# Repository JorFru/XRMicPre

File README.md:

XRMicPre
========

### Project on standby state. I already have a X32.

Mic preamp module for a poor man's digital mixer

History:
Behringer's XR12 and XR16 are a very powerful and cheap digital mixers, but don't have enough mic preamps for some applications.

This project allows you to get the full performance of this mixers on live and studio applications.

Desireable features:

- Combo entrada de micrófono con jack. jack hi-z
- 2x salida balanceada
- Control de la ganancia preciso y repetible. Control de ganancia con stepped o con potenciómetro digital + pantalla.
- HPF 80-100Hz
- Alimentación phantom (DC-DC/a baterías)

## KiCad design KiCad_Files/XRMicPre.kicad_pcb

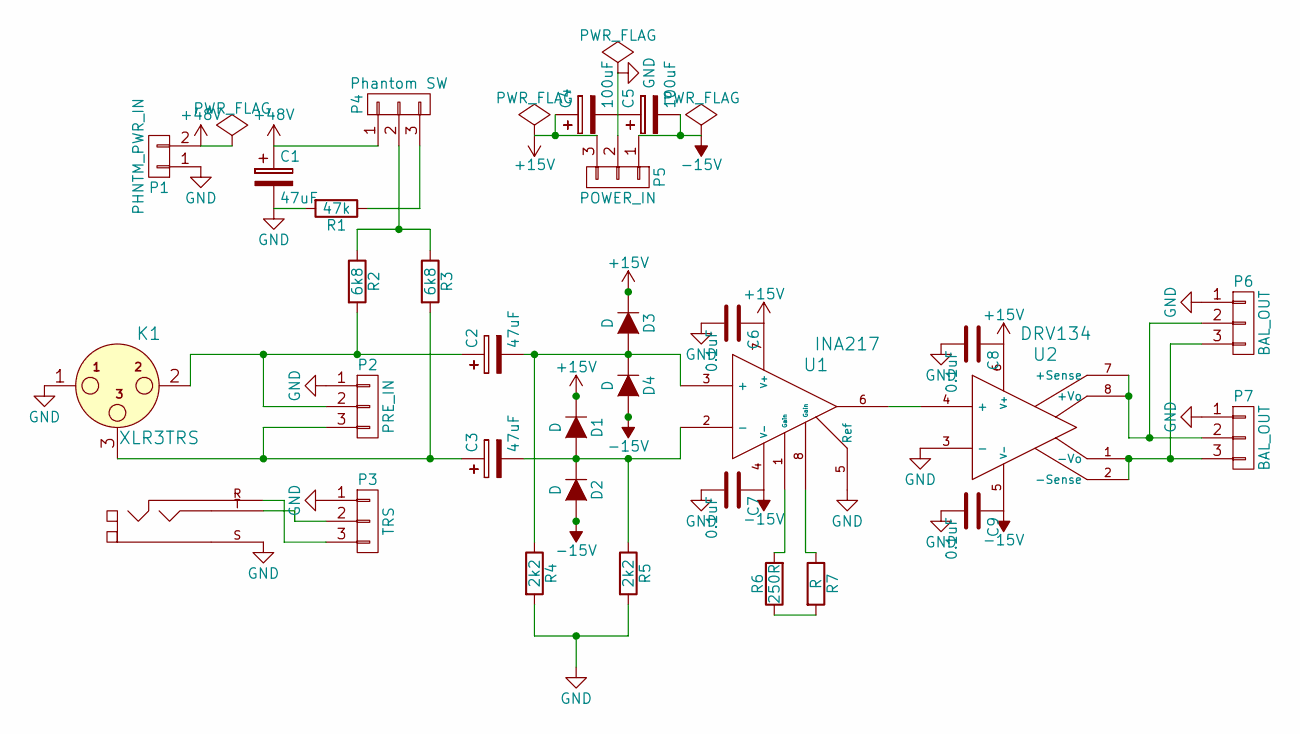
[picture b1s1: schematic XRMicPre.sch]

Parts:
C1, C2, C3: 47uF; C_Radial_D6.3_L11.2_P2.5
C4, C5: 100uF; C_Radial_D6.3_L11.2_P2.5
C6, C7, C8, C9: 0.1uF; C1-1
D1, D2, D3, D4: D; MiniMELF_Standard
K1: XLR3TRS; NCJ6FA-V
P1: PHNTM_PWR_IN; Socket_Strip_Straight_1x02
P2: PRE_IN; Socket_Strip_Straight_1x03
P3: TRS; Socket_Strip_Straight_1x03
P4: Phantom SW; Socket_Strip_Straight_1x03
P5: POWER_IN; Socket_Strip_Straight_1x03
P6, P7: BAL_OUT; Socket_Strip_Straight_1x03
R1: 47k; R_0805_HandSoldering
R2, R3: 6k8; R_0805_HandSoldering
R4, R5: 2k2; R_0805_HandSoldering
R6: 250R; R_0805_HandSoldering
R7: R; Socket_Strip_Straight_1x02
U1: INA217; DIP8+SOIC8_1
U2: DRV134; DIP8+SOIC8_1

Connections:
+15V: C4.1, C6.1, C8.1, D1.1 (K), D3.1 (K), P5.3, U1.7 (V+), U2.6 (V+)
+48V: C1.1, P1.2, P4.1
-15V: C5.2, C7.1, C9.1, D2.2 (A), D4.2 (A), P5.1, U1.4 (V-), U2.5 (V-)
GND: C1.2, C6.2, C7.2, C8.2, C9.2, K1.1, K1.S, P1.1, P2.1, P3.1, P5.2, P6.1, P7.1, R1.2, R4.2, R5.2, U1.5 (Ref), U2.3 (-)
unnamed: C2.1, K1.2, P2.2, R2.2
unnamed: C2.2, D3.2 (A), D4.1 (K), R4.1, U1.3 (+)
unnamed: C3.1, K1.3, P2.3, R3.2
unnamed: C3.2, D1.2 (A), D2.1 (K), R5.1, U1.2 (-)
unnamed: C4.2, C5.1
unnamed: K1.R, P3.3
unnamed: K1.T, P3.2
unnamed: P4.2, R2.1, R3.1
unnamed: P4.3, R1.1
unnamed: P6.2, P7.2, U2.7 (+Sense), U2.8 (+Vo)
unnamed: P6.3, P7.3, U2.1 (-Vo), U2.2 (-Sense)
unnamed: R6.1, R7.2
unnamed: R6.2, U1.1 (Gain)
unnamed: R7.1, U1.8 (Gain)
unnamed: U1.6, U2.4 (+)

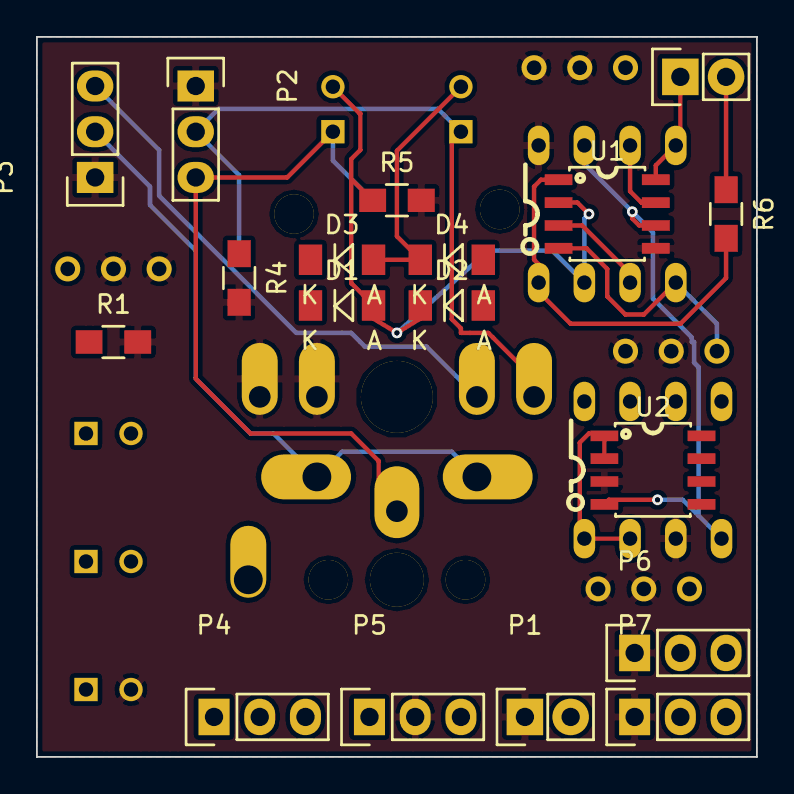
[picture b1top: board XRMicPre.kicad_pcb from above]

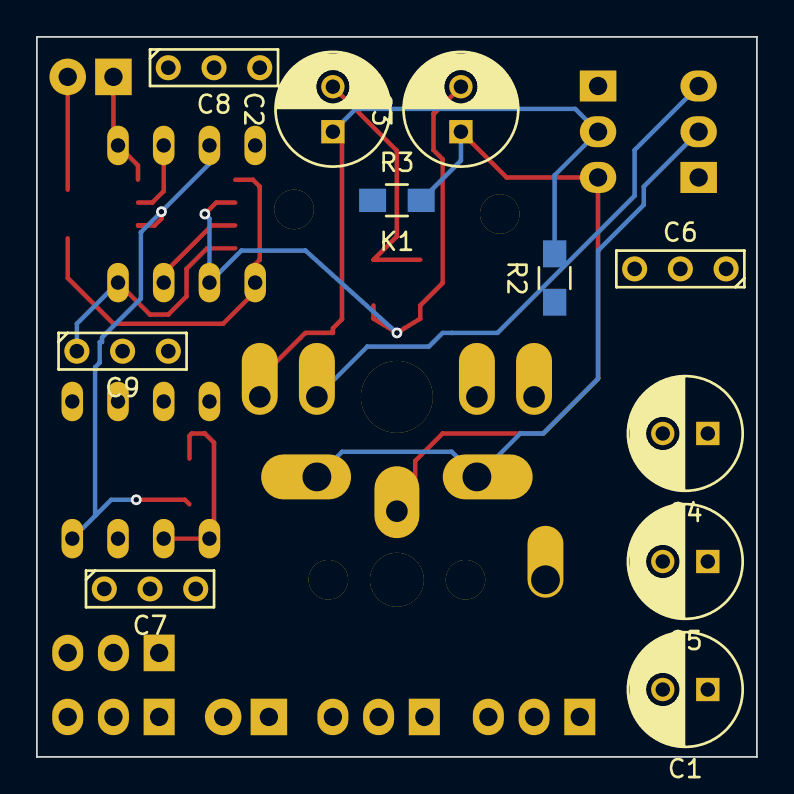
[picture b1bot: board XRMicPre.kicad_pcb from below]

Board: 2 copper layers, 40.0 x 40.0 mm, 30 parts (12 on the bottom side), 19 nets.

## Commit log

2016-03-17 Picture and readme upload
2016-03-18 Reduce picture weight
2016-03-18 Redimension pic
2016-03-18 Resized
2016-07-06 First commit for KiCad files
2016-07-07 Almost finished schematic
2016-08-25 Working on PCB
2016-08-28 minipinhead added
